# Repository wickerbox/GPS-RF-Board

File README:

Universal GPS RF Front-end Board

An RF front-end board that breaks out I and Q signals to serial, USB, and Ethernet for GPS receiver development. 

Several GPS receiver boards exist on the market to receive GPS satellite signals and process it to provide location data but these GPS receivers only give the final location. Getting access to the raw data before they go into correlators means you have to purchase a “RF front end” for hundreds of dollars, at which point you can work on projects like building an FPGA receiver board or developing a software radio receiver. 

Both of these projects are in-progress projects at Portland State, and are stalled on purchasing the very expensive RF front end. This project proposes to design, build, and release an open-source GPS receiver RF front-end board that would offer the GPS raw data over USB and serial outputs. Open source GPS receiver boards do exist, including in Andrew Greenberg’s GPL-GPS Master’s thesis, but all are based on very out dated and out-of-production GPS chipsets and are not easily acquired. 

Cost is also a factor: commercial RF front end boards are hundreds to thousands of dollars. And while the proposed chip for this project, the MAX2769 Universal GPS Receiver, costs only $5, the development kit is $600 -- in other words, cost prohibitive for a small project and frustrating for embedded software developers who may not have the time or experience to design and build their own hardware.

Current status: April 2013 hardware revision (v2)

Author: Jenner Hanni <wicker>
School: Portland State University

License: BSD "3 clause" license.

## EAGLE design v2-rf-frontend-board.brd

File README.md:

# GPS RF Board v2

Portland State University's Maseeh College of Engineering and Computer Science runs an innovation program that awards small thousand-dollar grants to students working on interesting projects. In 2011 there were a handful of GPS-related projects that needed a way to work directly with the raw I/Q data coming from the GPS satellites before any processing or correlating had been done. 

Commercial off-the-shelf GPS receivers are cheap and ubiquitous but they don't expose that data. One of my mentors, Andrew Greenberg, developed an open source GPS receiver for his Masters thesis in 2005 and suggested I take a look at doing the same thing with current hardware. I said I would if he would help, so together we built a board, built a revision, and are in the process of figuring out what modifications will be needed for a third.

The board isn't a full GPS receiver. Instead, it's an "RF front end" board that has a MAX2769 Universal GPS Receiver chip to read the GPS signals and pass them out over something that looks a lot like SPI but isn't. We chose to place an STM32F407 microcontroller running the ChibiOS embedded operating system on the board to support streaming the data out over Ethernet and USB. We exposed the raw pins over a header between the MAX2769 and STM32F407 to allow a user to skip the microcontroller entirely. We also included an SD card to log the data.

The board does not currently support a battery so it must be powered over USB or Ethernet at all times. 

This project is open hardware and software licensed under the 3-clause BSD license and maintained on the <a href="http://psas.pdx.edu/">Portland State Aerospace Society</a>'s <a href="http://github.com/psas/">Github account</a>. You can find the bill of materials and Eagle schematics at <a href="http://github.com/psas/gps-rf-board/">psas/gps-rf-board</a> and the software as part of <a href="http://githbu.com/psas/stm32/">psas/stm32</a>.

It's been a big group effort in the push to get it talking; Andrew, K, Theo, and Kenny at least have helped out with software and modwire soldering, and I might have missed someone. 

<h3>Board Layout Overview</h3>

The board has four layers and was ordered from <a href="http://oshpark.com">OSHPark</a>.

<h3>Power</h3>

We can power the board from Rocketnet Ethernet (up to 20V) or over USB (about 5V) so we used an LMZ12001 switching regulator with an input voltage range from 4.5V to 20V to output 3.3V for the digital side of the board. We then used two ultra-low noise MAX8510 LDO linear regulators to provide 2.85V on separate digital and analog supply lines for the RF side of the board. 

<h3>GPS</h3>

The <a href="http://datasheets.maximintegrated.com/en/ds/MAX2769.pdf">MAX2769</a> is a tiny 28-pin universal GPS Receiver with a 1.4dB noise figure. The datasheet says we don't need external SAW filters but we used them anyway. The chip has two LNA inputs and the eval kit is set up for to support both passive and active antennas. We used the <a href="http://datasheets.maximintegrated.com/en/ds/MAX2769EVKIT.pdf">MAX2769 Eval Kit</a> as a reference but it was a particularly difficult schematic to work with.

Our board has a single antenna attachment point with a couple of optional circuits that the user chooses by where you populate capacitors and resistors. Option #1 is whether or not to have an LNA1 and its ANTBIAS-pin power circuit. Option #2 is whether to put into LNA1 or LNA2 on the chip.  

<h3>Output</h3>

We use a 100-pin ARM Cortex-M3 STM32F407 running the Portland State Aerospace Society's version of ChibiOS to program the MAX2769 and to support USB, Ethernet, and an SD card. We also break out raw data signals at pin test points.

Ethernet requires the Portland State Aerospace Society's Rocketnet connector for programming, data streaming, and power. 

A micro-USB connector is available for programming, data streaming, and power. 

The micro-SD card is available for data logging.

The serial breakout is two 1x11 0.1" headers which we also used for debug. We ran traces between the two breakouts because we were unsure about some of the pinouts from the MAX2769 and wanted to be sure we could cut traces and easily run modwire. 

<h3>Build</h3>

This is the board installed on the avionics module that carries the flight computer, sensor packages, and battery packs. The green board on top is the commercial Crescent GPS unit. The purple board down below is the JennerGPS. They're both connected to the splitter in the middle, which runs off to the cylindrical patch antenna on the skin of the rocket. 

<h3>Current Status</h3>

The board was flown on the Portland State Aerospace Society's LV2.3 airframe for Launch 11 on July 20th, 2014, in Brothers, Oregon, to an altitude of 15,000 feet. The hardware was complete but the software on the board was not entirely ready for launch and, anyway, the entire GPS system failed so no data was retrieved. 

More information on the launch is available at <a href="http://psas.pdx.edu/launch11/">the PSAS Launch 11 page</a>.

<h3>Links and References</h3>

The <a href="http://github.com/psas/gps-rf-board/">Github repository</a> has all the schematics. The current version is v2. We welcome collaboration but do please contact us before using the schematics because the repo may not have all current modifications. 

It was super helpful to reference <a href="http://swift-nav.com/piksi.html">Swift Navigation's Piksi GPS Receiver</a> which uses the MAX2769 chip with an STM32F407 and FPGA.

The first version of this board was funded by the <a href="http://www.pdx.edu/cecs/innovation-program">MCECS Innovation Program</a>.

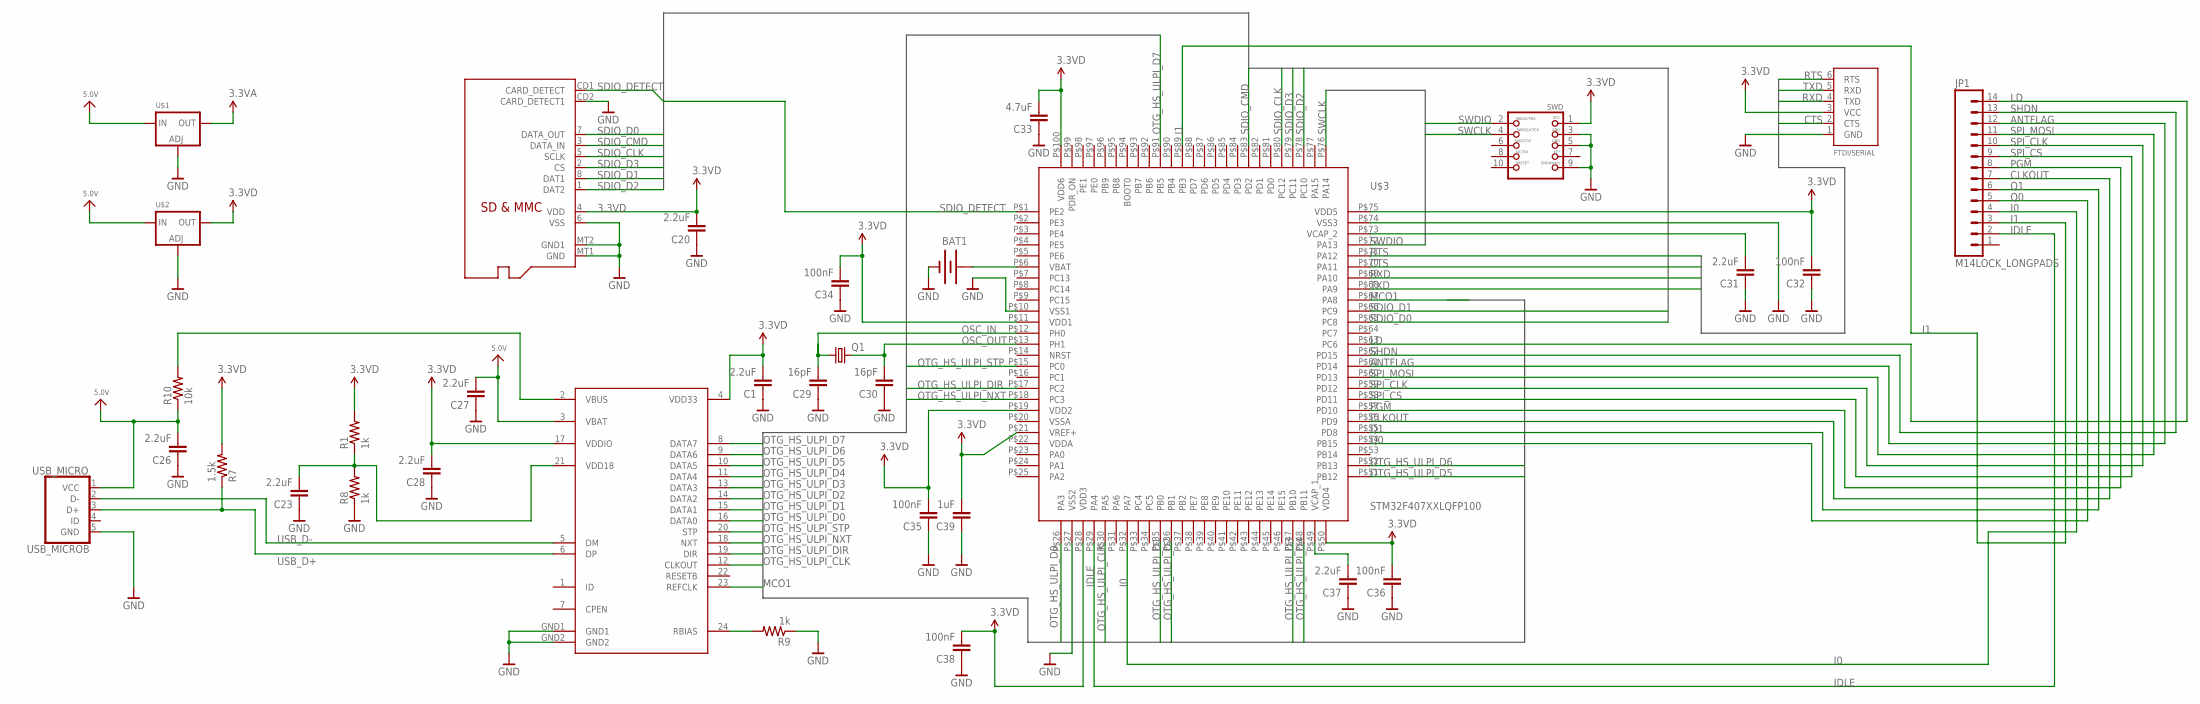
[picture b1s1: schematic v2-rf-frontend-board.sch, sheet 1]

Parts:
BAT1: BATTERY12MM; BATTCON_12MM
C1, C20, C23, C26, C27, C28, C31, C37: 2.2uF; C0402
C29, C30: 16pF; C0402
C32, C34, C35, C36, C38: 100nF; C0402
C33: 4.7uF; C0402
C39: 1uF; C0402
FTDI/SERIAL: FTDIUSBCABLE; 1X06_ROUND
HS_USB: USB3318; QFN-24-USB
JP1: M14LOCK_LONGPADS; 1X14_LOCK_LONGPADS
Q1: CRYSTALCTS406; CTS406
R1, R8, R9: 1k; R0402
R7: 1.5k; R0402
R10: 10k; R0402
SWD: JTAG-CORTEXM3MOLEX; CORTEXM3_SWD10_MOLEX
U$1, U$2: LM1117SOT223-REFLOW; SOT223-R
U$3: STM32F407XXLQFP100; LQFP100
U$5: MICROSD
USB_MICRO: USB_MICROB; MICRO-B-RA-TH

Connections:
3.3VA: U$1.2 (OUT); also elsewhere on the board
3.3VD: C1.2, C20.2, C28.2, C32.2, C33.2, C34.2, C35.2, C36.2, C38.2, C39.2, FTDI/SERIAL.3 (VCC), HS_USB.4 (VDD33), HS_USB.17 (VDDIO), R1.2, R7.2, SWD.1, U$2.2 (OUT), U$3.P$11 (VDD1), U$3.P$19 (VDD2), U$3.P$21 (VREF+), U$3.P$28 (VDD3), U$3.P$50 (VDD4), U$3.P$75 (VDD5), U$3.P$100 (VDD6), U$5.4 (VDD); also elsewhere on the board
5.0V: C26.2, C27.2, HS_USB.3 (VBAT), R10.1, U$1.3 (IN), U$2.3 (IN), USB_MICRO.1 (VCC)
ANTFLAG: JP1.12, U$3.P$61 (PD14); also elsewhere on the board
BAR_GND: BAT1.GND (-), C1.1, C20.1, C23.1, C26.1, C27.1, C28.1, C29.1, C30.1, C31.1, C32.1, C33.1, C34.1, C35.1, C36.1, C37.1, C38.1, C39.1, FTDI/SERIAL.1 (GND), HS_USB.GND1, HS_USB.GND2, R8.1, R9.1, SWD.3, SWD.5, SWD.9, U$1.1 (ADJ), U$2.1 (ADJ), U$3.P$10 (VSS1), U$3.P$27 (VSS2), U$3.P$74 (VSS3), U$5.6 (VSS), U$5.CD2 (CARD_DETECT1), U$5.MT1 (GND), U$5.MT2 (GND1), USB_MICRO.5 (GND); also elsewhere on the board
CLKOUT: JP1.7, U$3.P$56 (PD9); also elsewhere on the board
CTS: FTDI/SERIAL.2 (CTS), U$3.P$70 (PA11)
I0: JP1.4, U$3.P$32 (PA7); also elsewhere on the board
I1: JP1.3, U$3.P$89 (PB3); also elsewhere on the board
IDLE: JP1.2, U$3.P$29 (PA4)
LD: JP1.14, U$3.P$63 (PC6); also elsewhere on the board
MCO1: HS_USB.23 (REFCLK), U$3.P$67 (PA8)
unnamed: C23.2, HS_USB.21 (VDD18), R1.1, R8.2
unnamed: HS_USB.24 (RBIAS), R9.2
unnamed: C37.2, U$3.P$49 (VCAP_1)
OSC_IN: C29.2, Q1.1, U$3.P$12 (PH0)
OSC_OUT: C30.2, Q1.3 (2), U$3.P$13 (PH1)
OTG_HS_ULPI_CLK: HS_USB.12 (CLKOUT), U$3.P$30 (PA5)
OTG_HS_ULPI_D0: HS_USB.16 (DATA0), U$3.P$26 (PA3)
OTG_HS_ULPI_D1: HS_USB.15 (DATA1), U$3.P$35 (PB0)
OTG_HS_ULPI_D2: HS_USB.14 (DATA2), U$3.P$36 (PB1)
OTG_HS_ULPI_D3: HS_USB.13 (DATA3), U$3.P$47 (PB10)
OTG_HS_ULPI_D4: HS_USB.11 (DATA4), U$3.P$48 (PB11)
OTG_HS_ULPI_D5: HS_USB.10 (DATA5), U$3.P$51 (PB12)
OTG_HS_ULPI_D6: HS_USB.9 (DATA6), U$3.P$52 (PB13)
OTG_HS_ULPI_D7: HS_USB.8 (DATA7), U$3.P$91 (PB5)
OTG_HS_ULPI_DIR: HS_USB.19 (DIR), U$3.P$17 (PC2)
OTG_HS_ULPI_NXT: HS_USB.18 (NXT), U$3.P$18 (PC3)
OTG_HS_ULPI_STP: HS_USB.20 (STP), U$3.P$15 (PC0)
PGM: JP1.8, U$3.P$57 (PD10)
Q0: JP1.5, U$3.P$54 (PB15); also elsewhere on the board
Q1: JP1.6, U$3.P$55 (PD8); also elsewhere on the board
RTS: FTDI/SERIAL.6 (RTS), U$3.P$71 (PA12)
RXD: FTDI/SERIAL.4 (TXD), U$3.P$69 (PA10)
SDIO_CLK: U$3.P$80 (PC12), U$5.5 (SCLK)
SDIO_CMD: U$3.P$83 (PD2), U$5.3 (DATA_IN)
SDIO_D0: U$3.P$65 (PC8), U$5.7 (DATA_OUT)
SDIO_D1: U$3.P$66 (PC9), U$5.8 (DAT1)
SDIO_D2: U$3.P$78 (PC10), U$5.1 (DAT2)
SDIO_D3: U$3.P$79 (PC11), U$5.2 (CS)
SDIO_DETECT: U$3.P$1 (PE2), U$5.CD1 (CARD_DETECT)
SHDN: JP1.13, U$3.P$62 (PD15)
SPI_CLK: JP1.10, U$3.P$59 (PD12); also elsewhere on the board
SPI_CS: JP1.9, U$3.P$58 (PD11); also elsewhere on the board
SPI_MOSI: JP1.11, U$3.P$60 (PD13); also elsewhere on the board
SWCLK: SWD.4, U$3.P$76 (PA14)
SWDIO: SWD.2, U$3.P$72 (PA13)
TXD: FTDI/SERIAL.5 (RXD), U$3.P$68 (PA9)
USB_D+: HS_USB.6 (DP), R7.1, USB_MICRO.3 (D+)
USB_D-: HS_USB.5 (DM), USB_MICRO.2 (D-)
VBAT: BAT1.PWR@1 (+), U$3.P$6 (VBAT)
VBUS: HS_USB.2 (VBUS), R10.2
VCAP_2: C31.2, U$3.P$73 (VCAP_2)

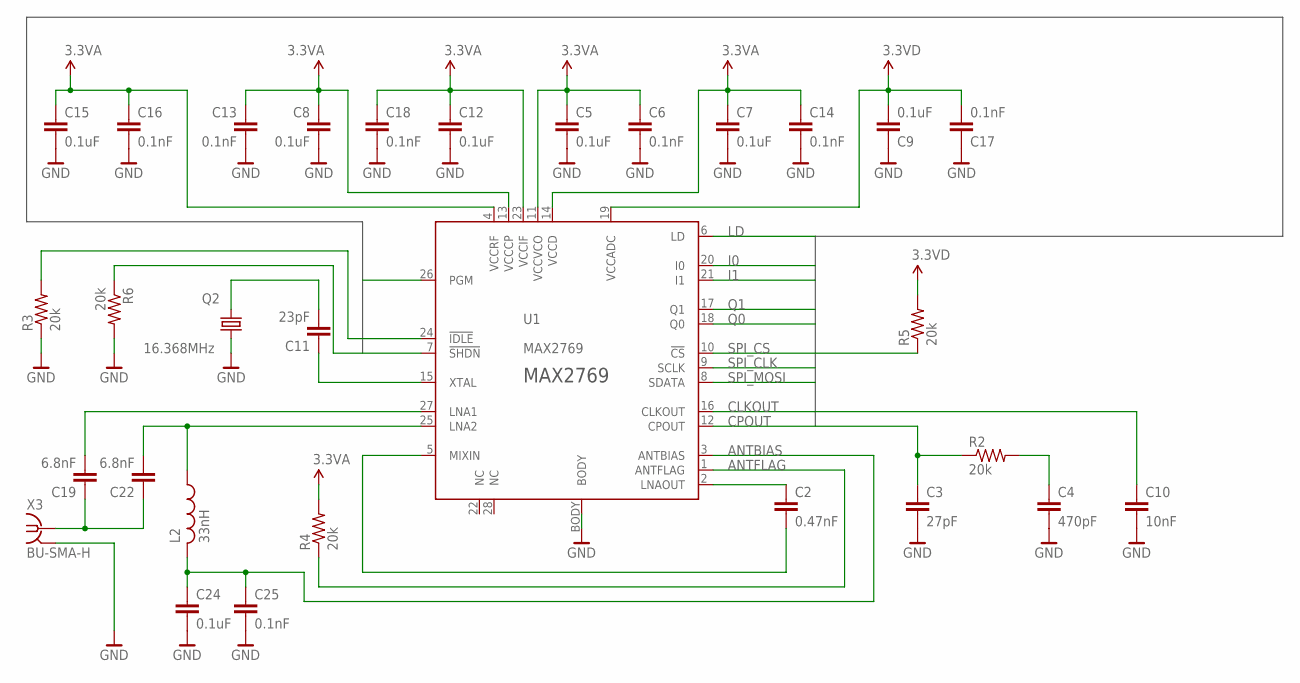
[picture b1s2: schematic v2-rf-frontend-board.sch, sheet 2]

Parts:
C2: 0.47nF; C0402
C3: 27pF; C0402
C4: 470pF; C0402
C5, C7, C8, C9, C12, C15, C24: 0.1uF; C0402
C6, C13, C14, C16, C17, C18, C25: 0.1nF; C0402
C10: 10nF; C0402
C11: 23pF; C0402
C19, C22: 6.8nF; C0402
L2: 33nH; 0402-A
Q2: 16.368MHz; CTS406
R2, R3, R4, R5, R6: 20k; R0402
U1: MAX2769; 90-0023
X3: BU-SMA-H

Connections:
3.3VA: C5.1, C6.1, C7.1, C8.1, C12.1, C13.1, C14.1, C15.1, C16.1, C18.1, R4.2, U1.4 (VCCRF), U1.11 (VCCVCO), U1.13 (VCCCP), U1.14 (VCCD), U1.23 (VCCIF); also elsewhere on the board
3.3VD: C9.2, C17.2, R5.2, U1.19 (VCCADC); also elsewhere on the board
ANTBIAS: C24.1, C25.1, L2.2, U1.3 (ANTBIAS)
ANTFLAG: R4.1, U1.1 (ANTFLAG); also elsewhere on the board
BAR_GND: C3.2, C4.2, C5.2, C6.2, C7.2, C8.2, C9.1, C10.2, C12.2, C13.2, C14.2, C15.2, C16.2, C17.1, C18.2, C24.2, C25.2, Q2.3 (2), R3.1, R6.2, U1.BODY, X3.2 (GND), X3.3 (GND), X3.4 (GND), X3.5 (GND); also elsewhere on the board
CLKOUT: C10.1, U1.16 (CLKOUT); also elsewhere on the board
CPOUT: C3.1, R2.1, U1.12 (CPOUT)
I0: U1.20 (I0); also elsewhere on the board
I1: U1.21 (I1); also elsewhere on the board
LD: U1.6 (LD); also elsewhere on the board
LNA1: C19.2, U1.27 (LNA1)
LNA2: C22.2, L2.1, U1.25 (LNA2)
LNAOUT: C2.1, U1.2 (LNAOUT)
unnamed: C19.1, C22.1, X3.1
unnamed: C11.2, Q2.1
unnamed: R6.1, U1.7 (!SHDN)
unnamed: R3.2, U1.24 (!IDLE)
unnamed: C2.2, U1.5 (MIXIN)
unnamed: C11.1, U1.15 (XTAL)
unnamed: C4.1, R2.2
Q0: U1.18 (Q0); also elsewhere on the board
Q1: U1.17 (Q1); also elsewhere on the board
SPI_CLK: U1.9 (SCLK); also elsewhere on the board
SPI_CS: R5.1, U1.10 (!CS); also elsewhere on the board
SPI_MOSI: U1.8 (SDATA); also elsewhere on the board

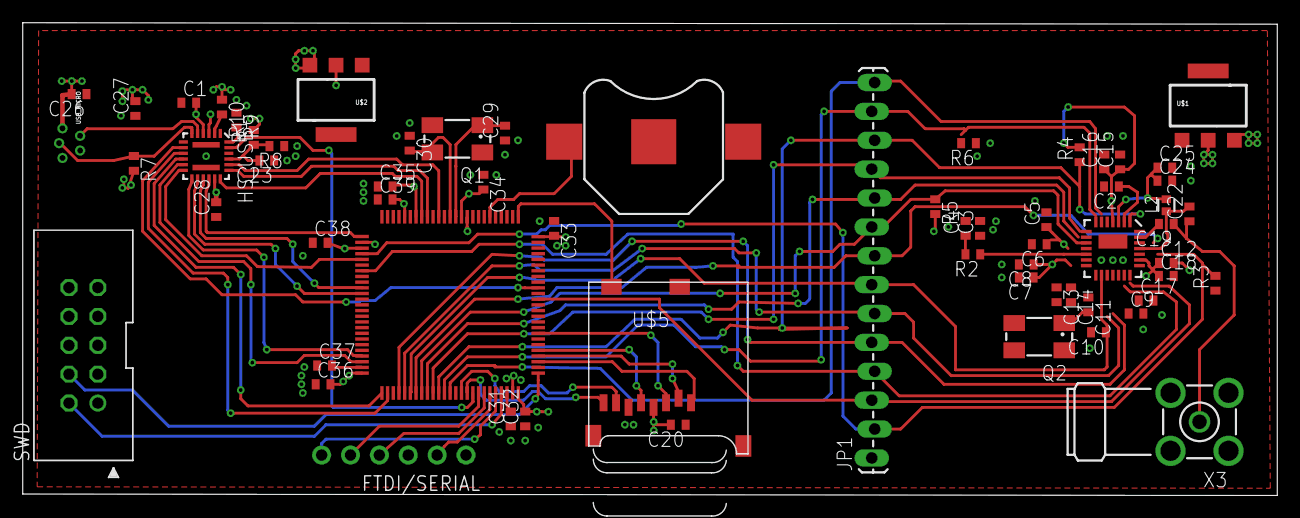
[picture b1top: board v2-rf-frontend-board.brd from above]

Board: 4 copper layers, 110.3 x 41.6 mm, 63 parts (0 on the bottom side), 65 nets.

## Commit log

2012-01-26 Created gh-pages branch via GitHub
2012-05-01 First commit.
2012-05-01 Starting to lay out connections for MAX2769.
2012-05-01 Took out the word plethora.
2012-05-01 Initial connections for MAX2769. No A or D VCC yet.
2012-05-28 Add SMA connectors. Add micro-B USB connector. Add SD-card connector. Verify MAX2769 connections. Clean up 3.3V and GND symbols for consistency.
2012-06-01 Lay and confirm all wires and elements EXCEPT terminal pinout on serial version of the board.
2012-06-01 Lay and confirm all wires off MAX2769 chip.
2012-06-01 ERC error free. Ready for layout.
2012-07-24 Add USB318 PHY and connect most of the pins to STM32F407 chip. Remove direct chip-miniUSB wiring.
2012-07-24 Finish USB PHY connections except RESET and REF.
2012-09-07 All peripherals on schema. Both chips connected. Verifying wiring. Power totally wrong still.
2012-09-07 Signal wiring good except SDIO. Needs power fixed.
2012-09-07 SDIO wired. Still needs power fixed.
2012-09-07 All 3.3v is either 3.3VA or 3.3VD for analog or digital. Only power issues are on STM board.
2012-09-07 Power wired to STM32F4. Chip looks good. How to wire BOOT?
2012-09-07 Swapped out crystal and reg for smaller packages.
2012-09-07 Got all parts on the board for the layout. General sense of things.
2012-09-07 Saving it before Andrew touches it.
2012-09-19 Add buses. Complete SDIO detect circuit. Add bypass caps where needed.
2012-09-19 All power pins replaced with customs so no ERC fails. Still needs BOOT0/PDR_ON on STM figured out.
2012-09-19 All ERC errors and warnings fixed or approved. No LEDs in place.
2012-09-19 Start layout on RF side.
2012-09-20 Started board layout with single ground and two power planes on second layer.
2012-10-02 Change layout for MAX2769 chip. RF header needs pin swap.
2012-10-02 RF side signals routed except for power.
2012-10-02 Fixed reversed P26,P28 reversed on STM32F4. Better layout on digital side. Incomplete.
2012-10-05 Layout done and verified. Fails Laen's DRU for layer setup issues.
2012-10-07 Final version sent to Laen for Dorkbot Order.
2012-10-24 Fixed facts.
2013-04-07 Cleaning repo.
2013-04-07 Updated README.
2013-04-07 Changed name scheme for ease of reading.
2013-04-07 Added .gitignore
2013-04-07 Added docs/
2013-04-07 Added library. Updated MAX2769 symbol.
2013-04-07 Changed MAX2769 symbol and fixed circuit.

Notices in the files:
parts and their libraries:
SparkFun-Connectors: Licensing: CC v3.0 Share-Alike You are welcome to use this library for commercial purposes.
